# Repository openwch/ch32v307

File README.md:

# 32-bit Interconnected RISC-V MCU CH32V307/CH32V317
EN | [中文](README_zh.md)

### Overview
The CH32V305 and CH32V307/CH32V317 are interconnected microcontrollers, based on 32-bit RISC-V core, with hardware stack area and fast interrupt entry. Compared with standard RISC-V, the interrupt response speed is greatly improved. With single-precision float point instruction sets added and stack area extended, the CH32V305/7 has higher performance, the number of U(S)ART is extended to 8, and the number of motor timer is extended to 4. The CH32V305/7 provides USB2.0 high-speed interface (480Mbps) and has built-in PHY transceiver. CH32V307 Ethernet MAC is upgraded to GbE and integrates 10M PHY module.CH32V317 integrates 10M/100M PHY module

### System Block Diagram

### Features
- RISC-V4F processor, max 144MHz system clock frequency, RV32IMAFC instruction set;
- Single-cycle multiplication and hardware division, hardware float point unit (FPU) ;
- 64KB SRAM，256KB Flash;
- Supply voltage: 2.5V/3.3V, GPIO unit is supplied independently;
- Multiple low-power modes: sleep/stop/standby;
- Power-on/power-down reset (POR/PDR), programmable voltage detector (PVD);
- 2 general DMA controllers, 18 channels in total;
- 4 amplifiers;
- Single true random number generator (TRNG)
- 2 x 12-bit DAC;
- 2-unit 16-channel 12-bit ADC, 16-channel TouchKey;
- 10 timers;
- USB2.0 full-speed OTG interface;
- USB2.0 high-speed host/device interface (built-in 480Mbps PHY)
- 3 USARTs, 5 UARTs;
- 2 CAN interfaces (2.0B active);
- SDIO interface, FSMC interface, DVP;
- 2 x I2C, 3 x SPI, 2 x IIS;
- CH32V307 built-in Ethernet 10M PHY
- CH32V317 built-in Ethernet 10M/100M PHY
- CH32V307 80 I/O ports, can be mapped to 16 external interrupts;
- CH32V317 70 I/O ports, can be mapped to 16 external interrupts;
- CRC calculation unit, 96-bit unique chip ID;
- Serial 2-wire debug interface;
- Packages: LQFP64M, LQFP100,QFN68（CH32V317WCU6）.

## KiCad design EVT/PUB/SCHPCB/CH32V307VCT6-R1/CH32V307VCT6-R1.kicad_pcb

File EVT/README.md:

# EVT

### -- download URL
*  CH32V307EVT.ZIP-https://www.wch.cn/downloads/CH32V307EVT_ZIP.html

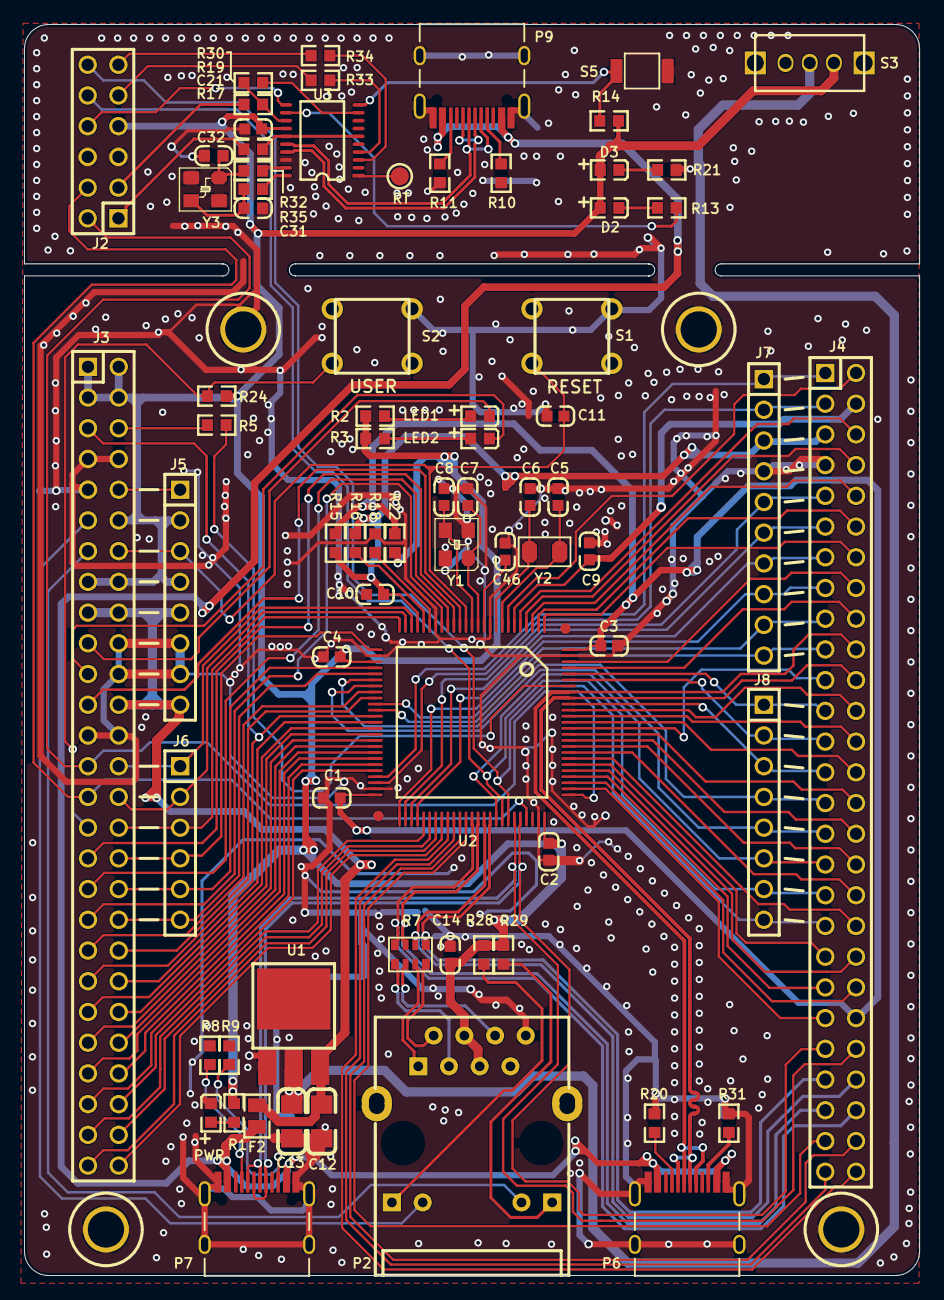
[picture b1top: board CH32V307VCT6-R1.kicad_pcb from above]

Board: 2 copper layers, 74.0 x 103.4 mm, 74 parts (0 on the bottom side), 137 nets.

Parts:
C1, C2, C3, C4, C9, C10, C11, C14, C21, C46: 0.1uF; 0603_C
C5, C6: 12pF; 0603_C
C7, C8: 22pF; 0603_C
C12, C13: 10uF; 3216_C
C31, C32: NC(22pF); 0603_C
D2: BLUE; 0603+
D3: RED; 0603+
F2: 500mA; 0805
J2: Header 6X2; IDC12-2.54mm
J3, J4: HEADER 27x2; IDC54-2.54MM
J5, J8: Header 8; SIP8-2.54mm
J6: Header 6; SIP6-2.54MM
J7: Header 10; SIP10-2.54mm
LED1: LED1 blue; 0603+
LED2: LED2 blue; 0603+
P2: HR911105A
P6: USBHS; TYPE-C-Receptacle-2.0
P7: USBFS; TYPE-C-Receptacle-2.0
P9: TYPE-C; TYPE-C-Receptacle-2.0
PWR: POWER red; 0603+
R1, R2, R3, R13, R21, R28, R29, R30: 1K; 0603
R5, R14, R24: 10K; 0603
R7: 0Ω; RCA-8P4R-0603
R8, R9, R10, R11, R20, R31: NC(5.1K); 0603
R15, R16, R18, R22: 0Ω; 0603
R17, R19: 100; 0603
R32, R35: NC(0R); 0603
R33, R34: 270; 0603
RT: Testpoint; TESTPOINT1
S1: RESET; KEYX
S2: USER; KEYX
S3: SW; SW1
S5: KEY; 贴片按键
U1: 1117-3.3V; SOT-223
U2: CH32V307V; LQFP100
U3: CH32V305F; TSSOP20
Y1: 8M; XT3225
Y2: 32.768k; FC-135
Y3: NC(12M); XT3225

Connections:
5V_in: F2.1, P6.A4, P6.B4, P7.A4, P7.B4, P9.A4, P9.B4
+5V: C12.1, F2.2, J3.17, J3.18, J3.24, J5.5, J5.8, U1.3
BOOT0: R5.2, U2.94
BOOT1: J3.5, J3.41, U2.37
CLK: J2.2, J3.27, U2.76
CLK0: J2.1, R17.1
DIO: J2.4, J3.29, U2.72
DIO0: J2.3, R19.1
D_SWCLK: R17.2, U3.6, U3.15
D_SWDIO: R19.2, R30.1, U3.13
ELED1: J3.11, P2.10
ELED2: J3.13, P2.11
ERXN: J4.49, R7.3, U2.64
ERXN1: P2.6, R7.6
ERXP: J4.50, R7.4, U2.63
ERXP1: P2.3, R7.5
ETXN: J4.47, R7.1, U2.66
ETXN1: P2.2, R7.8
ETXP: J4.48, R7.2, U2.65
ETXP1: P2.1, R7.7
GND: C1.1, C2.1, C3.2, C4.1, C5.2, C6.2, C7.1, C8.1, C9.1, C10.1, C11.1, C12.2, C13.2, C14.1, C21.2, C31.1, C32.1, C46.2, J2.5, J2.6, J3.7, J3.8, J3.9, J3.20, J3.22, J3.25, J3.26, J4.7, J5.6, J5.7, J7.4, P2.8, P6.0, P6.A1, P6.B1, P7.0, P7.A1, P7.B1, P9.0, P9.A1, P9.B1, PWR.2, R8.1, R9.1, R10.2, R11.2, R18.1, R20.1, R21.1, R31.1, S1.3, S2.3, S5.2, U1.1, U2.10, U2.19, U2.27, U2.49, U2.74, U2.99, U3.18, Y1.2, Y1.4, Y3.2, Y3.4
IAP: R14.1, S5.1, U3.10
KEY: J3.31, R24.1, S2.1
LED1: J3.19, LED1.2
LED2: J3.21, LED2.2
LED_CON: R13.1, U3.12
NRST: C11.2, J3.14, J5.3, S1.1, U2.14
NetC13_1: C13.1, S3.1, U1.2
NetD2_2: D2.2, R13.2
NetD3_2: D3.2, R21.2
NetJ3_6: J3.6, R5.1
NetJ3_10: J3.10, J5.1
NetLED1_1: LED1.1, R2.2
NetLED2_1: LED2.1, R3.2
NetP2_9: P2.9, R28.2
NetP2_12: P2.12, R29.2
NetP6_A5: P6.A5, R20.2
NetP6_B5: P6.B5, R31.2
NetP7_A5: P7.A5, R8.2
NetP7_B5: P7.B5, R9.2
NetP9_A5: P9.A5, R10.1
NetP9_B5: P9.B5, R11.1
NetPWR_1: PWR.1, R1.1
OSC_IN: C32.2, R32.2, Y3.1
OSC_OUT: C31.2, R35.2, Y3.3
PA0: J3.28, J6.1, U2.23
PA1: J3.30, J6.2, U2.24
PA2: J3.32, J6.3, U2.25
PA3: J3.34, J6.4, U2.26
PA4: J3.36, J6.5, U2.29
PA5: J3.38, J6.6, U2.30
PA6: J4.29, J8.4, U2.31
PA7: J4.31, J8.5, U2.32
PA8: J4.33, J8.6, U2.67
PA9: J2.10, J4.35, J8.7, U2.68
PA10: J2.12, J4.37, J8.8, U2.69
PA11: J4.46, P7.A7, P7.B7, U2.70
PA12: J4.45, P7.A6, P7.B6, U2.71
PA15: J4.43, U2.77
PB0: J4.17, J7.9, U2.35
PB1: J4.19, J7.10, U2.36
PB3: J4.26, U2.89
PB4: J4.24, U2.90
PB5: J4.27, J8.3, U2.91
PB6: J4.22, P6.A7, P6.B7, U2.92
PB7: J4.20, P6.A6, P6.B6, U2.93
PB8: J4.25, J8.2, U2.95
PB9: J4.23, J8.1, U2.96
PB10: J4.1, J7.1, U2.47
PB11: J4.3, J7.2, U2.48
PB12: J4.15, J7.8, U2.51
PB13: J4.9, J7.5, U2.52
PB14: J4.11, J7.6, U2.53
PB15: J4.13, J7.7, U2.54
PC0: J3.23, U2.15
PC1: J3.33, U2.16
PC2: J3.35, U2.17
PC3: J3.37, U2.18
PC4: J3.39, U2.33
PC5: J3.40, U2.34
PC6_305: R30.2, U3.9
PC10: J4.42, U2.78
PC11: J4.41, U2.79
PC12: J4.40, U2.80
PC13: J4.2, U2.7
PC14: C5.1, U2.8, Y2.1
PC15: C6.1, U2.9, Y2.2
PD0: J4.39, U2.81
PD0_305: R32.1, U3.19
PD1: J4.38, U2.82
PD1_305: R35.1, U3.20
PD2: J4.36, U2.83
PD3: J4.34, U2.84
PD4: J4.32, U2.85
PD5: J4.30, U2.86
PD6: J4.21, U2.87
PD7: J4.28, U2.88
PD8: J3.51, U2.55
PD9: J3.52, U2.56
PD10: J3.53, U2.57
PD11: J3.54, U2.58
PD12: J4.54, U2.59
PD13: J4.53, U2.60
PD14: J4.52, U2.61
PD15: J4.51, U2.62
PE0: J4.18, U2.97
PE1: J4.16, U2.98
PE2: J4.14, U2.1
PE3: J4.12, U2.2
PE4: J4.10, U2.3
PE5: J4.8, U2.4
PE6: J4.6, U2.5
PE7: J3.42, U2.38
PE8: J3.43, U2.39
PE9: J3.44, U2.40
PE10: J3.45, U2.41
PE11: J3.46, U2.42
PE12: J3.47, U2.43
PE13: J3.48, U2.44
PE14: J3.49, U2.45
PE15: J3.50, U2.46
RST0: J2.8, U3.11
RT: RT.1, U3.1
RX_OUT: J2.9, R33.1
TX_OUT: J2.11, R34.1
UART3_RX: R33.2, U3.4
UART3_TX: R34.2, U3.3
USB_N: P9.A7, P9.B7, U3.16
USB_P: P9.A6, P9.B6, U3.17
VBAT: C9.2, J4.4, U2.6
VCC: C2.2, C4.2, C14.2, C21.1, C46.1, D2.1, D3.1, J2.7, J3.1, J3.2, J3.3, J3.4, J3.12, J3.15, J3.16, J5.2, J5.4, P2.4, P2.5, R1.2, R2.1, R3.1, R14.2, R22.2, R24.2, R28.1, R29.1, S3.3, U2.11, U2.28, U2.75, U3.14
VDDA: C10.2, J4.5, J7.3, R15.2, R16.1, U2.22
VIO: C1.2, C3.1, J4.44, R15.1, R22.1, U2.50, U2.100
VREF+: R16.2, U2.21
VREF-: R18.2, U2.20
XI: C7.2, U2.12, Y1.1
XO: C8.2, U2.13, Y1.3

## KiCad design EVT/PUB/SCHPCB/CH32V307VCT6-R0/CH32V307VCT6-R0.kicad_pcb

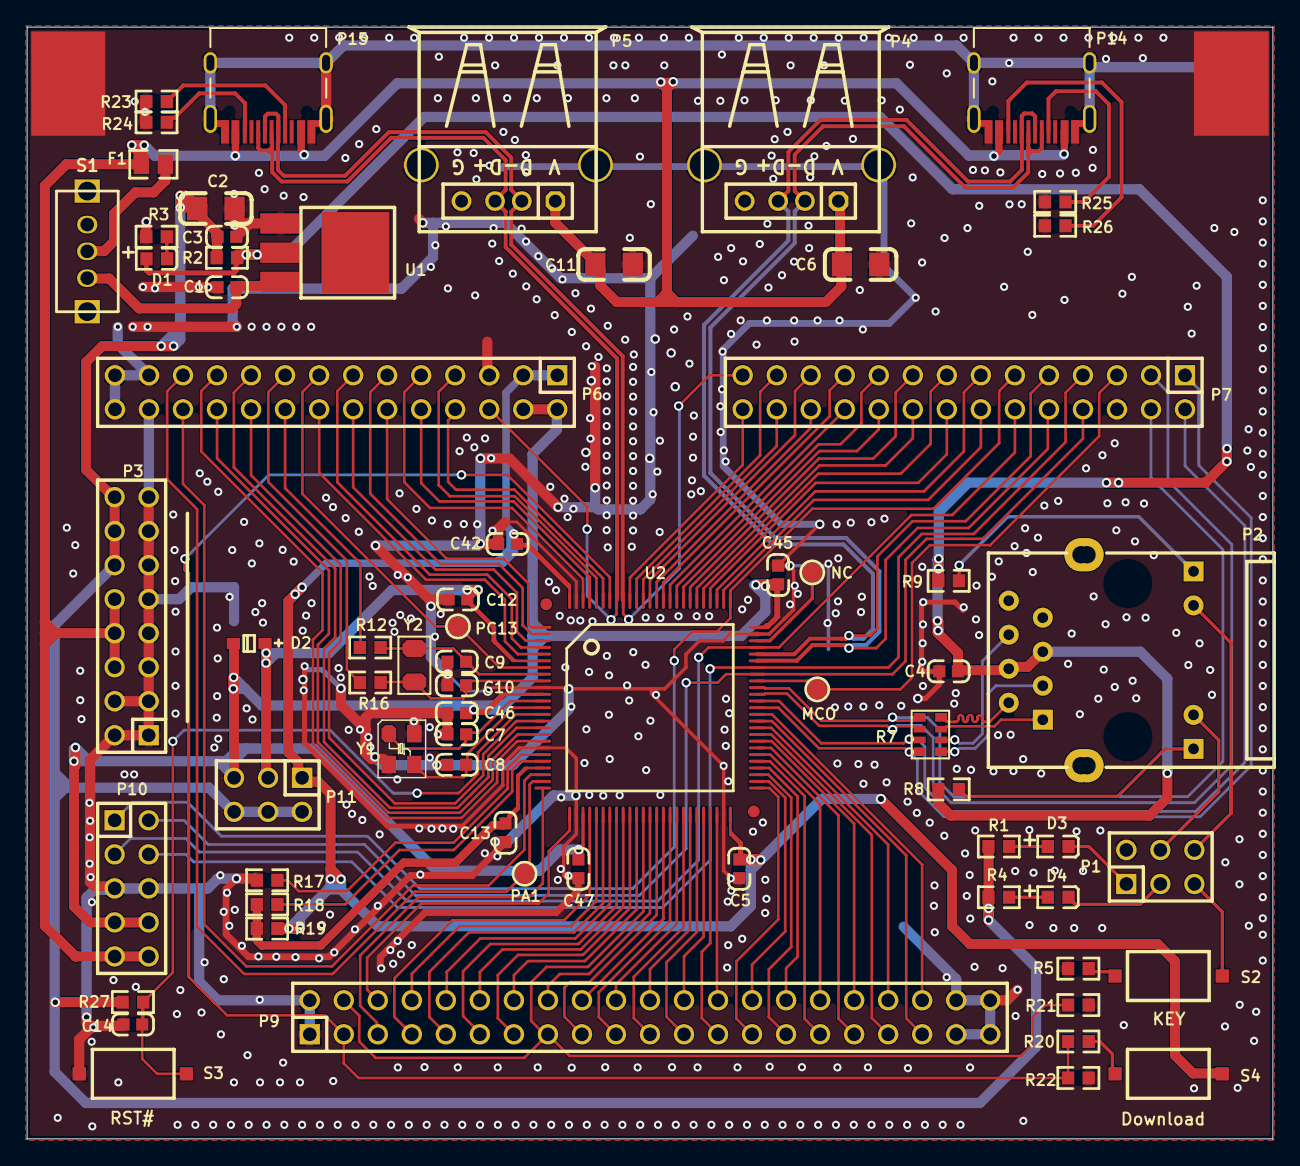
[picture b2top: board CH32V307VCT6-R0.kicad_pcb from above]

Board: 2 copper layers, 93.0 x 83.0 mm, 68 parts (0 on the bottom side), 119 nets.

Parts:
C1, C3, C4, C5, C12, C13, C14, C42, C45, C46, C47: 0.1uF; 0603_C
C2, C6, C11: 10uF; 3216_C
C7, C8: 22pF; 0603_C
C9, C10: 12pF; 0603_C
D1, D4: RED; 0603+
D2: B0520WS; SOD-323
D3: BLUE; 0603+
F1: 500mA; 0805
MCO: Testpoint; TESTPOINT1
NC: Testpoint; TESTPOINT1
P1: IO; IDC6-2.54mm
P2: HR911105A
P3: Ppin; IDC16-2.54mm
P4: USBFS; USBAF
P5: USBHS; USBAF
P6, P7: HEADER 14x2; IDC28-2.54MM
P9: HEADER 21x2; IDC42-2.54MM
P10: LINK; IDC10-2.54mm
P11: Psel; IDC6-2.54mm
P14: USBFS; TYPE-C-Receptacle-2.0
P15: USBHS; TYPE-C-Receptacle-2.0
PA1: Testpoint; TESTPOINT1
PC13: Testpoint; TESTPOINT1
R1, R3, R4, R8, R9, R20: 1K; 0603
R2, R17, R18, R19: 0R; 0603
R5, R21, R22, R27: 10K; 0603
R7: 0Ω; RCA-8P4R-0603
R12, R16: NC(0R); 0603
R23, R24, R25, R26: 5.1K; 0603
S1: SW SPDT; KEY2
S2: KEY; SMD_6.1x3.65x2.5mm-KEY
S3: RST#; SMD_6.1x3.65x2.5mm-KEY
S4: Download; SMD_6.1x3.65x2.5mm-KEY
U1: 1117-3.3V; SOT-223
U2: CH32V307V; LQFP100
Y1: 8MHz; XT3225
Y2: 32768Hz; FC-135

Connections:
3V3: C2.1, C3.1, P3.12, P3.14, P3.16, P11.2, P11.4, P11.6, R1.1, R2.1, R4.1, R27.2
3V3S: C4.2, D1.1, P2.4, P2.5, R2.2, R8.1, R9.1, U1.2
5V: C6.1, C11.1, F1.1, P3.6, P3.8, P3.10, P4.1, P5.1, P10.9, P10.10, P14.A4, P14.B4, P15.A4, P15.B4
BOOT0: P9.3, R20.1, R22.1, U2.94
BOOT1: P9.4, P9.15, R21.1, U2.37
ELED1: P1.4, P2.10
ELED2: P1.6, P2.11
ERXN: P7.2, R7.3, U2.64
ERXN1: P2.6, R7.6
ERXP: P7.1, R7.4, U2.63
ERXP1: P2.3, R7.5
ETXN: P7.4, R7.1, U2.66
ETXN1: P2.2, R7.8
ETXP: P7.3, R7.2, U2.65
ETXP1: P2.1, R7.7
GND: C1.2, C2.2, C3.2, C4.1, C5.2, C6.2, C7.1, C8.1, C9.1, C10.1, C11.2, C12.1, C13.2, C14.1, C42.1, C45.2, C46.2, C47.1, P1.2, P2.8, P3.1, P3.2, P3.3, P3.4, P3.5, P3.7, P3.9, P3.11, P3.13, P3.15, P4.0, P4.4, P5.0, P5.4, P6.5, P6.25, P6.26, P6.27, P6.28, P7.6, P9.1, P9.2, P9.39, P9.40, P9.41, P9.42, P10.5, P10.6, P14.0, P14.A1, P14.B1, P15.0, P15.A1, P15.B1, R3.2, R5.1, R17.1, R21.2, R22.2, R23.2, R24.2, R25.2, R26.2, S3.1, U1.1, U2.10, U2.19, U2.27, U2.49, U2.74, U2.99, Y1.2, Y1.4
KEY: P1.5, S2.1
LED1: D3.2, P1.1
LED2: D4.2, P1.3
MCO: MCO.1, P7.5, U2.67
NC: NC.1, U2.73
NRST: C14.2, R27.1, S3.2, U2.14
NetC1_1: C1.1, S1.2, U1.3
NetD1_2: D1.2, R3.1
NetD3_1: D3.1, R1.2
NetD4_1: D4.1, R4.2
NetF1_2: F1.2, S1.1
NetP2_9: P2.9, R8.2
NetP2_12: P2.12, R9.2
NetP14_A5: P14.A5, R25.1
NetP14_B5: P14.B5, R26.1
NetP15_A5: P15.A5, R23.1
NetP15_B5: P15.B5, R24.1
NetR5_2: R5.2, S2.2
NetR20_2: R20.2, S4.2
PA0: P6.24, U2.23
PA1: P6.23, PA1.1, U2.24
PA2: P9.5, U2.25
PA3: P9.6, U2.26
PA4: P9.7, U2.29
PA5: P9.8, U2.30
PA6: P9.9, U2.31
PA7: P9.10, U2.32
PA9: P7.8, P10.2, U2.68
PA10: P7.7, P10.4, U2.69
PA11: P4.2, P7.10, P14.A7, P14.B7, U2.70
PA12: P4.3, P7.9, P14.A6, P14.B6, U2.71
PA13: P7.12, P10.3, U2.72
PA14: P7.11, P10.1, U2.76
PA15: P7.14, U2.77
PB0: P9.13, U2.35
PB1: P9.14, U2.36
PB3: P7.26, U2.89
PB4: P7.25, U2.90
PB5: P7.28, U2.91
PB6: P5.2, P7.27, P15.A7, P15.B7, U2.92
PB7: P5.3, P6.6, P15.A6, P15.B6, U2.93
PB8: P6.8, U2.95
PB9: P6.7, U2.96
PB10: P9.25, U2.47
PB11: P9.26, U2.48
PB12: P9.27, U2.51
PB13: P9.28, U2.52
PB14: P9.29, U2.53
PB15: P9.30, U2.54
PC0: P6.20, U2.15
PC1: P6.19, U2.16
PC2: P6.22, U2.17
PC3: P6.21, U2.18
PC4: P9.11, U2.33
PC5: P9.12, U2.34
PC10: P7.13, U2.78
PC11: P7.16, U2.79
PC12: P7.15, U2.80
PC13: P6.15, PC13.1, U2.7
PC14: P6.18, R12.1
PC15: P6.17, R16.1
PD0: P7.18, U2.81
PD1: P7.17, U2.82
PD2: P7.20, U2.83
PD3: P7.19, U2.84
PD4: P7.22, U2.85
PD5: P7.21, U2.86
PD6: P7.24, U2.87
PD7: P7.23, U2.88
PD8: P9.31, U2.55
PD9: P9.32, U2.56
PD10: P9.33, U2.57
PD11: P9.34, U2.58
PD12: P9.35, U2.59
PD13: P9.36, U2.60
PD14: P9.37, U2.61
PD15: P9.38, U2.62
PE0: P6.10, U2.97
PE1: P6.9, U2.98
PE2: P6.12, U2.1
PE3: P6.11, U2.2
PE4: P6.14, U2.3
PE5: P6.13, U2.4
PE6: P6.16, U2.5
PE7: P9.16, U2.38
PE8: P9.17, U2.39
PE9: P9.18, U2.40
PE10: P9.19, U2.41
PE11: P9.20, U2.42
PE12: P9.21, U2.43
PE13: P9.22, U2.44
PE14: P9.23, U2.45
PE15: P9.24, U2.46
VBAT: C12.2, D2.1, P11.3, U2.6
VDD: C45.1, C46.1, C47.2, D2.2, P6.2, P6.4, P10.7, P10.8, P11.5, U2.11, U2.28, U2.75
VDDA: C13.1, R18.1, R19.2, U2.22
VIO: C5.1, C42.2, P6.1, P6.3, P11.1, R19.1, S4.1, U2.50, U2.100
VREF+: R18.2, U2.21
VREF-: R17.2, U2.20
X32KI: C9.2, R12.2, U2.8, Y2.1
X32KO: C10.2, R16.2, U2.9, Y2.2
XI: C7.2, U2.12, Y1.1
XO: C8.2, U2.13, Y1.3

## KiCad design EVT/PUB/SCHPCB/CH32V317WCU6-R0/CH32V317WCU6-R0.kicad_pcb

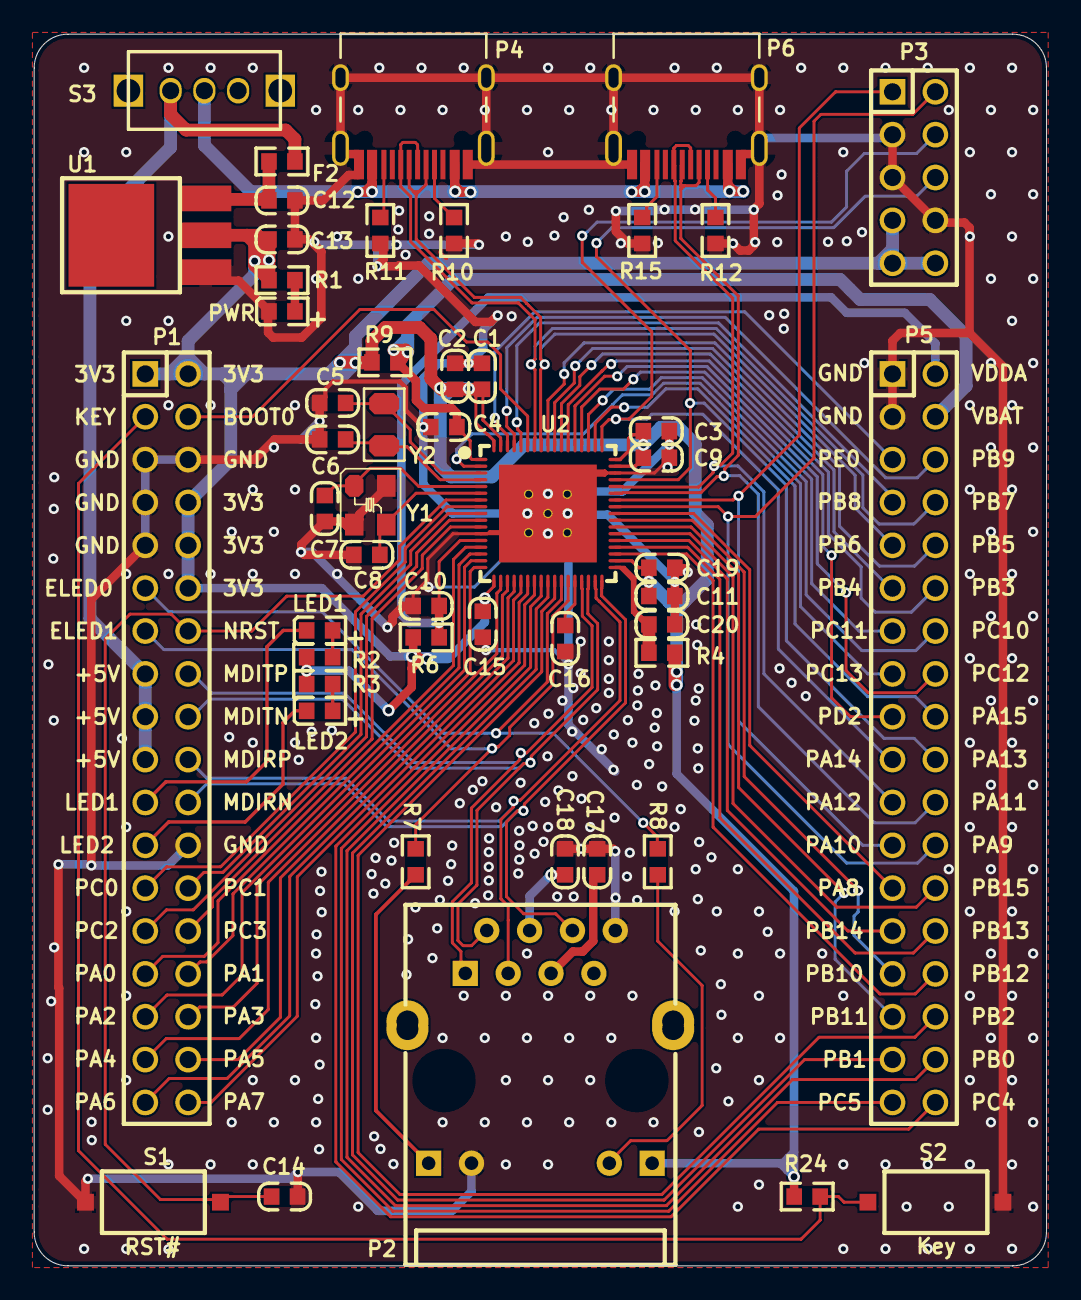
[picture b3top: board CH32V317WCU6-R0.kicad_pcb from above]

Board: 2 copper layers, 60.0 x 73.0 mm, 50 parts (0 on the bottom side), 79 nets.

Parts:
C1, C2, C3, C4, C9, C10, C11, C14, C15, C17, C18: 0.1uF; 0603_C
C5, C6: 12pF; 0603_C
C7, C8: 20pF; 0603_C
C12, C13, C19: 10uF; 0603_C
C16, C20: 1uF; 0603_C
F2: 500mA; 0603
LED1: LED1 blue; 0603+
LED2: LED2 blue; 0603+
P1, P5: Header 18X2; IDC36-2.54mm
P2: HR911105A
P3: Header 5X2; IDC10-2.54mm
P4: USBHS; TYPE-C-Receptacle-2.0
P6: USBFS; TYPE-C-Receptacle-2.0
PWR: POWER red; 0603+
R1, R2, R3: 1K; 0603
R4: 0Ω; 0603
R6, R9: 0R; 0603
R7, R8: 470Ω; 0603
R10, R11, R12, R15: NC(5.1K); 0603
R24: 10K; 0603
S1: RST#; SMD_6.1x3.65x2.5mm-KEY
S2: Key; SMD_6.1x3.65x2.5mm-KEY
S3: SW; SW1
U1: 1117-3.3V; SOT-223
U2: CH32V317W; QFN68_8X8
Y1: 8M; XT3225
Y2: 32.768k; FC-135

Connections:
3V3: C1.2, C2.2, C3.2, C9.2, C11.2, C13.1, C15.2, C19.2, P1.1, P1.2, P1.8, P1.10, P1.12, P2.12, P3.7, P3.9, P3.10, R1.2, R2.1, R3.1, R4.2, R6.1, R9.1, R24.2, U1.2, U2.18, U2.36, U2.50, U2.51, U2.67, U2.68
5V: P4.A4, P4.B4, P6.A4, P6.B4, S3.1
+5V: F2.1, P1.15, P1.17, P1.19, S3.3
BOOT0: P1.4, U2.63
ELED0: P1.11, R8.1, U2.28
ELED1: P1.13, R7.1, U2.29
GND: C1.1, C2.1, C3.1, C4.1, C5.2, C6.2, C7.1, C8.1, C9.1, C10.2, C11.1, C12.2, C13.2, C14.1, C15.1, C16.1, C17.1, C18.1, C19.1, C20.1, P1.5, P1.6, P1.7, P1.9, P1.24, P2.8, P2.10, P3.3, P3.5, P3.8, P4.0, P4.A1, P4.B1, P5.1, P5.3, P6.0, P6.A1, P6.B1, PWR.2, R10.1, R11.1, R12.1, R15.1, S1.1, S2.2, U1.1, U2.0, U2.12, U2.49, Y1.2, Y1.4
KEY: P1.3, R24.1, S2.1
LED1: LED1.2, P1.21
LED2: LED2.2, P1.23
MDIRN: P1.22, P2.6, U2.34
MDIRP: P1.20, P2.3, U2.33
MDITN: P1.18, P2.2, U2.32
MDITP: P1.16, P2.1, U2.31
NRST: C14.2, P1.14, S1.2, U2.7
NetC12_1: C12.1, F2.2, U1.3
NetC17_2: C17.2, P2.5
NetC18_2: C18.2, P2.4
NetLED1_1: LED1.1, R2.2
NetLED2_1: LED2.1, R3.2
NetP2_9: P2.9, R7.2
NetP2_11: P2.11, R8.2
NetP4_A5: P4.A5, R10.2
NetP4_B5: P4.B5, R11.2
NetP6_A5: P6.A5, R12.2
NetP6_B5: P6.B5, R15.2
NetPWR_1: PWR.1, R1.1
PA0: P1.29, U2.14
PA1: P1.30, U2.15
PA2: P1.31, U2.16
PA3: P1.32, U2.17
PA4: P1.33, U2.19
PA5: P1.34, U2.20
PA6: P1.35, U2.21
PA7: P1.36, U2.22
PA8: P5.25, U2.43
PA9: P3.2, P5.24, U2.44
PA10: P3.1, P5.23, U2.45
PA11: P5.22, P6.A7, P6.B7, U2.46
PA12: P5.21, P6.A6, P6.B6, U2.47
PA13: P3.6, P5.20, U2.48
PA14: P3.4, P5.19, U2.52
PA15: P5.18, U2.53
PB0: P5.34, U2.25
PB1: P5.33, U2.26
PB2: P5.32, U2.27
PB3: P5.12, U2.58
PB4: P5.11, U2.59
PB5: P5.10, U2.60
PB6: P4.A7, P4.B7, P5.9, U2.61
PB7: P4.A6, P4.B6, P5.8, U2.62
PB8: P5.7, U2.64
PB9: P5.6, U2.65
PB10: P5.29, U2.42
PB11: P5.31, U2.41
PB12: P5.30, U2.37
PB13: P5.28, U2.38
PB14: P5.27, U2.39
PB15: P5.26, U2.40
PC0: P1.25, U2.8
PC1: P1.26, U2.9
PC2: P1.27, U2.10
PC3: P1.28, U2.11
PC4: P5.36, U2.23
PC5: P5.35, U2.24
PC10: P5.14, U2.54
PC11: P5.13, U2.55
PC12: P5.16, U2.56
PC13: P5.15, U2.2
PD2: P5.17, U2.57
PE0: P5.5, U2.66
VBAT: C4.2, P5.4, R9.2, U2.1
VDDA: C10.1, P5.2, R6.2, U2.13
VDDK: C16.2, U2.30
VDD_ETH: C20.2, R4.1, U2.35
X32KI: C5.1, U2.3, Y2.1
X32KO: C6.1, U2.4, Y2.2
XI: C7.2, U2.5, Y1.1
XO: C8.2, U2.6, Y1.3

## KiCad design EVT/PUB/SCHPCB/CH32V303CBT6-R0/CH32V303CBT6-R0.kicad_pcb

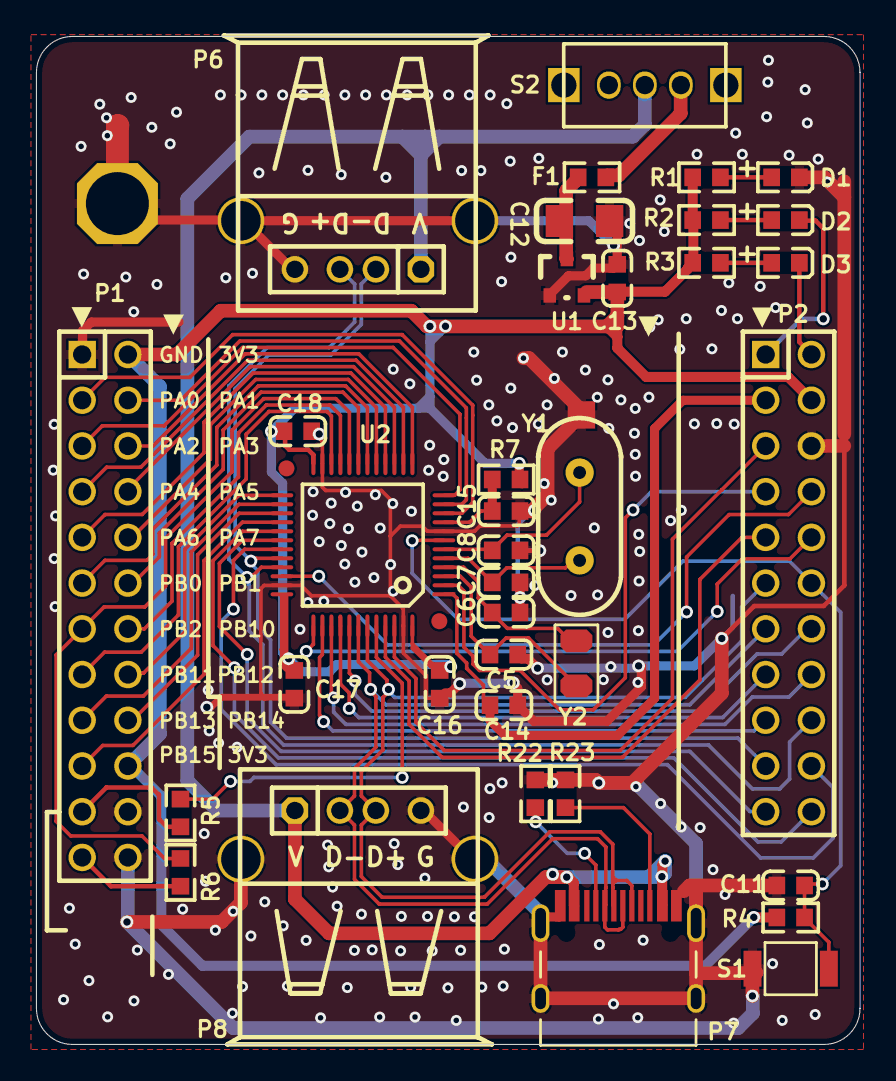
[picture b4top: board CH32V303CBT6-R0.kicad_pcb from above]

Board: 2 copper layers, 45.8 x 56.0 mm, 36 parts (0 on the bottom side), 55 nets.

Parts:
C5, C6: 12pF; 0603_C
C7, C8: 22pF; 0603_C
C11, C14, C15, C16, C17, C18: 0.1uF; 0603_C
C12: 10uF; 3216_C
C13: 2.2uF; 0603_C
D1: POWER red; 0603+
D2: LED1; 0603+
D3: LED2; 0603+
F1: 500mA; 0603
P1: HEADER 12x2; IDC24-2.54MM
P2: HEADER 11x2; IDC22-2.54MM
P6, P8: USB_A; USBAF
P7: TYPE-C; TYPE-C-Receptacle-2.0
R1, R2, R3: 1K; 0603
R4, R5, R6: 10K; 0603
R7: 0Ω; 0603
R22, R23: NC(5.1K); 0603
S1: KEY; 贴片按键
S2: SW; KEY2
U1: 6219P33M; SOT-23
U2: CH32V203CxT; LQFP48
Y1: 8M; XT_AT49
Y2: 32.768k; FC-135

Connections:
+5V: P6.1, P7.A4, P7.B4, P8.1, S2.1
BOOT0: R5.1, U2.44
BOOT1: P1.13, R6.1, U2.20
GND: C5.2, C6.2, C7.1, C8.1, C11.1, C12.2, C13.2, C14.2, C15.2, C16.1, C17.1, C18.1, D1.2, P1.1, P1.22, P1.24, P2.6, P6.0, P6.4, P7.0, P7.A1, P7.B1, P8.0, P8.4, R22.2, R23.2, S1.2, U1.1, U2.8, U2.23, U2.35, U2.47, Y1.0
LED1: D2.2, P2.1
LED2: D3.2, P2.2
NRST: C11.2, P2.12, R4.1, S1.1, U2.7
NetD1_1: D1.1, R1.1
NetD2_1: D2.1, R2.2
NetD3_1: D3.1, R3.2
NetF1_1: F1.1, S2.3
NetP1_21: P1.21, R5.2
NetP1_23: P1.23, R6.2
NetP7_A5: P7.A5, R22.1
NetP7_B5: P7.B5, R23.1
PA0: P1.3, U2.10
PA1: P1.4, U2.11
PA2: P1.5, U2.12
PA3: P1.6, U2.13
PA4: P1.7, U2.14
PA5: P1.8, U2.15
PA6: P1.9, U2.16
PA7: P1.10, U2.17
PA8: P2.22, U2.29
PA9: P2.21, U2.30
PA10: P2.20, U2.31
PA11: P2.19, P6.2, U2.32
PA12: P2.18, P6.3, U2.33
PA13: P2.8, U2.34
PA14: P2.10, U2.37
PA15: P2.17, U2.38
PB0: P1.11, U2.18
PB1: P1.12, U2.19
PB3: P2.16, U2.39
PB4: P2.15, U2.40
PB5: P2.14, U2.41
PB6: P2.13, P7.A7, P7.B7, P8.2, U2.42
PB7: P2.11, P7.A6, P7.B6, P8.3, U2.43
PB8: P2.9, U2.45
PB9: P2.5, U2.46
PB10: P1.14, U2.21
PB11: P1.15, U2.22
PB12: P1.16, U2.25
PB13: P1.17, U2.26
PB14: P1.18, U2.27
PB15: P1.19, U2.28
PC13: P2.7, U2.2
PC14: C5.1, U2.3, Y2.1
PC15: C6.1, U2.4, Y2.2
PD0: C7.2, U2.5, Y1.2
PD1: C8.2, U2.6, Y1.1
V5V: C12.1, F1.2, U1.3
VBAT: C14.1, P2.3, U2.1
VCC: C13.1, C16.2, C17.2, C18.2, P1.2, P1.20, P2.4, R1.2, R2.1, R3.1, R4.2, R7.1, U1.2, U2.24, U2.36, U2.48
VDDA: C15.1, R7.2, U2.9

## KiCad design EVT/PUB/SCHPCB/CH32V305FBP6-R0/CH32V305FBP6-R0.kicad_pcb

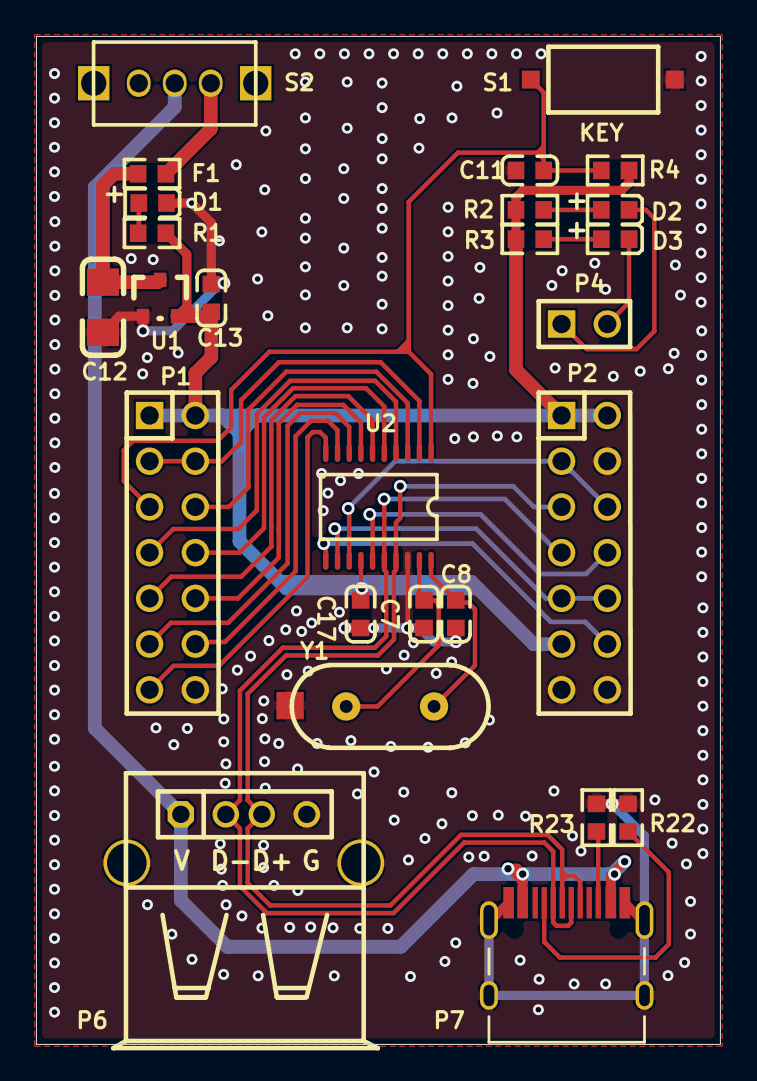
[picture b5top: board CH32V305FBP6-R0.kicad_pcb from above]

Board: 2 copper layers, 38.0 x 56.0 mm, 26 parts (0 on the bottom side), 30 nets.

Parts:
C7, C8: 22pF; 0603_C
C11, C17: 0.1uF; 0603_C
C12: 10uF; 3216_C
C13: 2.2uF; 0603_C
D1: POWER red; 0603+
D2: LED1; 0603+
D3: LED2; 0603+
F1: 500mA; 0603
P1, P2: HEADER 7x2; IDC14-2.54mm
P4: 2HEAD; SIP2-2.54mm
P6: USB_A; USBAF
P7: TYPE-C; TYPE-C-Receptacle-2.0
R1, R2, R3: 1K; 0603
R4: 10K; 0603
R22, R23: NC(5.1K); 0603
S1: KEY; SMD_6.1x3.65x2.5mm-KEY
S2: SW; KEY2
U1: 6219; SOT-23
U2: CH32V305F; TSSOP20
Y1: 8M; XT_AT49

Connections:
+5V: P6.1, P7.A4, P7.B4, S2.1
GND: C7.1, C8.1, C11.1, C12.2, C13.1, C17.1, D1.2, P1.14, P2.4, P2.13, P2.14, P6.0, P6.4, P7.0, P7.A1, P7.B1, R22.2, R23.2, S1.2, U1.1, U2.18, Y1.0
LED1: D2.2, P4.1
LED2: D3.2, P4.2
NRST: C11.2, P1.5, R4.1, S1.1, U2.1
NetD1_1: D1.1, R1.1
NetD2_1: D2.1, R2.2
NetD3_1: D3.1, R3.2
NetF1_1: F1.1, S2.3
NetP7_A5: P7.A5, R22.1
NetP7_B5: P7.B5, R23.1
PA1: P1.3, P1.4, U2.2
PA8: P2.9, P2.10, U2.12
PA9: P2.3, P2.6, U2.13
PA14: P2.8, U2.15
PB6: P2.7, P6.2, P7.A7, P7.B7, U2.16
PB7: P2.5, P6.3, P7.A6, P7.B6, U2.17
PB10: P1.6, U2.3
PB11: P1.7, U2.4
PB12: P1.8, U2.5
PB13: P1.9, U2.6
PB14: P1.10, U2.7
PB15: P1.11, U2.8
PC6: P1.12, U2.9
PC7: P1.13, U2.10
PC8: P2.12, U2.11
PD0: C7.2, U2.19, Y1.2
PD1: C8.2, U2.20, Y1.1
V5V: C12.1, F1.2, U1.3
VCC: C13.2, C17.2, P1.1, P1.2, P2.1, P2.2, P2.11, R1.2, R2.1, R3.1, R4.2, U1.2, U2.14

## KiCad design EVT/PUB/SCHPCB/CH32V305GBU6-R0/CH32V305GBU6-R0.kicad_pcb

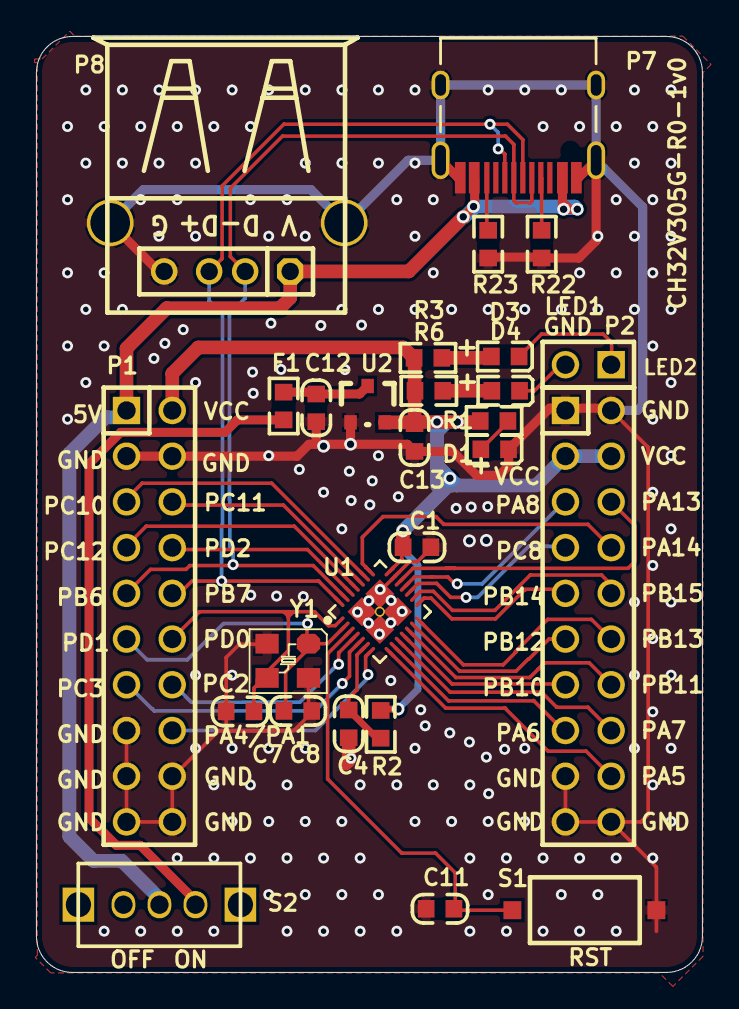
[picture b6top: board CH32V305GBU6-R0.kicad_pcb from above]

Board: 2 copper layers, 37.0 x 52.0 mm, 27 parts (0 on the bottom side), 38 nets.

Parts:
C1, C4, C11: 0.1uF; 0603_C
C7, C8: 22pF; 0603_C
C12: 10uF; 0603_C
C13: 2.2uF; 0603_C
D1: POWER red; 0603+
D3: LED2; 0603+
D4: LED1; 0603+
F1: 500mA; 0603
P1, P2: Header 10X2; IDC20-2.54mm
P4: HEADER 2; SIP2-2.54mm
P7: TYPE-C; TYPE-C-Receptacle-2.0
P8: USB_A; USBAF
R1, R2, R3, R6: 1K; 0603
R22, R23: 5.1K; 0603
S1: RST; SMD_6.1x3.65x2.5mm-KEY
S2: SW; SW1
U1: CH32V305GBU6; QFN28_4X4
U2: 6219P33M; SOT-23
Y1: 8M; XT3225

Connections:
GND: C1.2, C4.2, C7.1, C8.1, C11.1, C12.2, C13.2, D1.2, P1.3, P1.4, P1.15, P1.17, P1.18, P1.19, P1.20, P2.1, P2.2, P2.17, P2.19, P2.20, P7.0, P7.A1, P7.B1, P8.0, P8.4, R22.2, R23.2, S1.2, U1.0, U1.20, U2.1, Y1.2, Y1.4
LED1: D4.2, P4.2
LED2: D3.2, P4.1
NetD1_1: D1.1, R1.1
NetD3_1: D3.1, R3.2
NetD4_1: D4.1, R6.2
NetF1_1: F1.1, S2.3
NetP7_A5: P7.A5, R22.1
NetP7_B5: P7.B5, R23.1
PA4/PA1: P1.16, U1.7
PA5: P2.18, U1.8
PA6: P2.15, U1.9
PA7: P2.16, U1.10
PA8: P2.5, U1.18
PA13: P2.6, U1.19
PA14: P2.8, U1.22
PB6: P1.9, P7.A7, P7.B7, P8.2, U1.27
PB7: P1.10, P7.A6, P7.B6, P8.3, U1.28
PB10: P2.13, U1.11
PB11: P2.14, U1.12
PB12: P2.11, U1.13
PB13: P2.12, U1.14
PB14: P2.9, U1.15
PB15: P2.10, U1.16
PC2: P1.14, U1.4
PC3: P1.13, U1.5
PC8: P2.7, U1.17
PC10: P1.5, U1.23
PC11: P1.6, U1.24
PC12: P1.7, U1.25
PD0: C7.2, P1.12, U1.1, Y1.3
PD1: C8.2, P1.11, U1.2, Y1.1
PD2: P1.8, U1.26
RST: C11.2, S1.1, U1.3
V5V: C12.1, F1.2, U2.3
VBUS: P1.1, P7.A4, P7.B4, P8.1, S2.1
VCC: C1.1, C13.1, P1.2, P2.3, P2.4, R1.2, R2.1, R3.1, R6.1, U1.21, U2.2
VIO: C4.1, R2.2, U1.6

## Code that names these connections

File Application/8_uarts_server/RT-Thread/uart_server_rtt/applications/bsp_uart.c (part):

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 *
 *  @brief   initialize uart1~uart8 io
 *
 *           UART1  TX-->PA9   RX-->PA10
 *           UART2  TX-->PA2   RX-->PA3
 *           UART3  TX-->PB10  RX-->PB11
 *           UART4  TX-->PC10  RX-->PC11
 *           UART5  TX-->PC12  RX-->PD2
 *           UART6  TX-->PC0   RX-->PC1
 *           UART7  TX-->PC2   RX-->PC3
 *           UART8  TX-->PC4   RX-->PC5
 *
 *  @param   none
 *
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    		               RCC_APB2Periph_GPIOC|RCC_APB2Periph_GPIOD, ENABLE);


    /* UART1 TX-->PA9   RX-->PA10 */
//	GPIO_InitStructure.GPIO_Pin = GPIO_Pin_9;
//	GPIO_InitStructure.GPIO_Speed = GPIO_Speed_50MHz;
//	GPIO_InitStructure.GPIO_Mode = GPIO_Mode_AF_PP;
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//	GPIO_Init(GPIOA, &GPIO_InitStructure);


    /* USART2 TX-->PA2   RX-->PA3 */
    GPIO_InitStructure.GPIO_Pin = GPIO_Pin_2;
    GPIO_InitStructure.GPIO_Speed = GPIO_Speed_50MHz;
    GPIO_InitStructure.GPIO_Mode = GPIO_Mode_AF_PP;
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    GPIO_Init(GPIOA, &GPIO_InitStructure);


    /* USART3 TX-->PB10  RX-->PB11 */
	GPIO_InitStructure.GPIO_Pin = GPIO_Pin_10;
	GPIO_InitStructure.GPIO_Speed = GPIO_Speed_50MHz;
	GPIO_InitStructure.GPIO_Mode = GPIO_Mode_AF_PP;
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	GPIO_InitStructure.GPIO_Mode = GPIO_Mode_IN_FLOATING;
	GPIO_Init(GPIOB, &GPIO_InitStructure);

	/* USART4 TX-->PC10  RX-->PC11 */
	GPIO_InitStructure.GPIO_Pin = GPIO_Pin_10;
	GPIO_InitStructure.GPIO_Speed = GPIO_Speed_50MHz;
	GPIO_InitStructure.GPIO_Mode = GPIO_Mode_AF_PP;
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	GPIO_InitStructure.GPIO_Mode = GPIO_Mode_IN_FLOATING;
	GPIO_Init(GPIOC, &GPIO_InitStructure);

	/* USART5 TX-->PC12  RX-->PD2 */
	GPIO_InitStructure.GPIO_Pin = GPIO_Pin_12;
	GPIO_InitStructure.GPIO_Speed = GPIO_Speed_50MHz;
	GPIO_InitStructure.GPIO_Mode = GPIO_Mode_AF_PP;
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	GPIO_InitStructure.GPIO_Mode = GPIO_Mode_IN_FLOATING;
	GPIO_Init(GPIOD, &GPIO_InitStructure);

	/* USART6 TX-->PC0  RX-->PC1 */
	GPIO_InitStructure.GPIO_Pin = GPIO_Pin_0;
	GPIO_InitStructure.GPIO_Speed = GPIO_Speed_50MHz;
	GPIO_InitStructure.GPIO_Mode = GPIO_Mode_AF_PP;
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	GPIO_InitStructure.GPIO_Mode = GPIO_Mode_IN_FLOATING;
	GPIO_Init(GPIOC, &GPIO_InitStructure);

	/* USART7 TX-->PC2  RX-->PC3 */
	GPIO_InitStructure.GPIO_Pin = GPIO_Pin_2;
	GPIO_InitStructure.GPIO_Speed = GPIO_Speed_50MHz;
	GPIO_InitStructure.GPIO_Mode = GPIO_Mode_AF_PP;
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	GPIO_InitStructure.GPIO_Mode = GPIO_Mode_IN_FLOATING;
	GPIO_Init(GPIOC, &GPIO_InitStructure);

	/* USART8 TX-->PC4  RX-->PC5 */
	GPIO_InitStructure.GPIO_Pin = GPIO_Pin_4;
	GPIO_InitStructure.GPIO_Speed = GPIO_Speed_50MHz;
	GPIO_InitStructure.GPIO_Mode = GPIO_Mode_AF_PP;
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	UART_GPIO_Init();
	USART_InitTypeDef USART_InitStructure={0};

	/* USART1 TX-->PA9   RX-->PA10 */
//	uart_data_t[0].RX_buffer = &UART1_RX_DMA_DataBuf[0];
//	uart_data_t[0].TX_buffer = &UART1_TX_DMA_DataBuf[0];
//	uart_data_t[0].TX_data_length = &UART1_TX_Buf_Length[0];
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//	USART_Init(USART1, &USART_InitStructure);
//	USART_Cmd(USART1, ENABLE);

	/* USART2 TX-->PA2   RX-->PA3 */
	uart_data_t[1].RX_buffer = &UART2_RX_DMA_DataBuf[0];
	uart_data_t[1].TX_buffer = &UART2_TX_DMA_DataBuf[0];
	uart_data_t[1].TX_data_length = &UART2_TX_Buf_Length[0];
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	USART_Init(USART2, &USART_InitStructure);
	USART_Cmd(USART2, ENABLE);

	/* USART3 TX-->PB10  RX-->PB11 */
	uart_data_t[2].RX_buffer = &UART3_RX_DMA_DataBuf[0];
	uart_data_t[2].TX_buffer = &UART3_TX_DMA_DataBuf[0];
	uart_data_t[2].TX_data_length = &UART3_TX_Buf_Length[0];
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	USART_Cmd(USART3, ENABLE);


	/* USART4 TX-->PC10  RX-->PC11 */
	uart_data_t[3].RX_buffer = &UART4_RX_DMA_DataBuf[0];
	uart_data_t[3].TX_buffer = &UART4_TX_DMA_DataBuf[0];
	uart_data_t[3].TX_data_length = &UART4_TX_Buf_Length[0];
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    USART_Init(UART4, &USART_InitStructure);
    USART_Cmd(UART4, ENABLE);

	/* USART5 TX-->PC12  RX-->PD2 */
	uart_data_t[4].RX_buffer = &UART5_RX_DMA_DataBuf[0];
	uart_data_t[4].TX_buffer = &UART5_TX_DMA_DataBuf[0];
	uart_data_t[4].TX_data_length = &UART5_TX_Buf_Length[0];
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    USART_Init(UART5, &USART_InitStructure);
    USART_Cmd(UART5, ENABLE);

	/* USART6 TX-->PC0  RX-->PC1 */
	uart_data_t[5].RX_buffer = &UART6_RX_DMA_DataBuf[0];
	uart_data_t[5].TX_buffer = &UART6_TX_DMA_DataBuf[0];
	uart_data_t[5].TX_data_length = &UART6_TX_Buf_Length[0];
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    USART_Init(UART6, &USART_InitStructure);
    USART_Cmd(UART6, ENABLE);

	/* UART7  TX-->PC2   RX-->PC3 */
	uart_data_t[6].RX_buffer = &UART7_RX_DMA_DataBuf[0];
	uart_data_t[6].TX_buffer = &UART7_TX_DMA_DataBuf[0];
	uart_data_t[6].TX_data_length = &UART7_TX_Buf_Length[0];
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    USART_Cmd(UART7, ENABLE);


	/* UART8  TX-->PC4   RX-->PC5 */
	uart_data_t[7].RX_buffer = &UART8_RX_DMA_DataBuf[0];
	uart_data_t[7].TX_buffer = &UART8_TX_DMA_DataBuf[0];
	uart_data_t[7].TX_data_length = &UART8_TX_Buf_Length[0];
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
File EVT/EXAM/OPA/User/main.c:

/********************************** (C) COPYRIGHT *******************************
* File Name          : main.c
* Author             : WCH
* Version            : V1.0.0
* Date               : 2021/06/06
* Description        : Main program body.
*********************************************************************************
* Copyright (c) 2021 Nanjing Qinheng Microelectronics Co., Ltd.
* Attention: This software (modified or not) and binary are used for 
* microcontroller manufactured by Nanjing Qinheng Microelectronics.
*******************************************************************************/

/*
 *@Note
 OPA4 is used as voltage follower output, DAC outputs to OPA4, ADC samples OPA4
 DAC_CH1--PA4
 OPA4_CHP1--PC4
 OPA4_CHN1--PC3
 OPA4_OUT_IO_OUT0--PA0

  In this example, PA0 and PC3 are short-circuited, and PA4 is connected to PC4.
  If the negative feedback is connected to a resistor, it can also form an
  operational amplifier.
*/

#include "debug.h"

/* Global define */


/* Global Variable */ 
s16 Calibrattion_Val = 0;


/*********************************************************************
 * @fn      OPA4_Init
 *
 * @brief   Initializes OPA4 collection.
 *
 * @return  none
 */
void OPA4_Init(void)
{
    GPIO_InitTypeDef GPIO_InitStructure={0};
    OPA_InitTypeDef  OPA_InitStructure={0};

    RCC_APB2PeriphClockCmd(RCC_APB2Periph_GPIOC, ENABLE );
    GPIO_InitStructure.GPIO_Pin = GPIO_Pin_4|GPIO_Pin_3;
    GPIO_InitStructure.GPIO_Mode = GPIO_Mode_IN_FLOATING;
    GPIO_InitStructure.GPIO_Speed = GPIO_Speed_50MHz;
    GPIO_Init(GPIOC, &GPIO_InitStructure);

    OPA_InitStructure.OPA_NUM=OPA4;
    OPA_InitStructure.PSEL=CHP1;
    OPA_InitStructure.NSEL=CHN1;
    OPA_InitStructure.Mode=OUT_IO_OUT0;
    OPA_Init(&OPA_InitStructure);
    OPA_Cmd(OPA4,ENABLE);

}

/*********************************************************************
 * @fn      Dac_Channel1_Init
 *
 * @brief   Initializes DAC Channel1 collection.
 *
 * @return  none
 */
void Dac_Channel1_Init(void)
{
	GPIO_InitTypeDef GPIO_InitStructure={0};
	DAC_InitTypeDef DAC_InitType={0};
	
	RCC_APB2PeriphClockCmd(RCC_APB2Periph_GPIOA, ENABLE );
	RCC_APB1PeriphClockCmd(RCC_APB1Periph_DAC, ENABLE );
	
	GPIO_InitStructure.GPIO_Pin = GPIO_Pin_4;
 	GPIO_InitStructure.GPIO_Mode = GPIO_Mode_AIN; 		     
 	GPIO_InitStructure.GPIO_Speed = GPIO_Speed_50MHz;
 	GPIO_Init(GPIOA, &GPIO_InitStructure);
	GPIO_SetBits(GPIOA,GPIO_Pin_4);
	
	DAC_InitType.DAC_Trigger=DAC_Trigger_None;
	DAC_InitType.DAC_WaveGeneration=DAC_WaveGeneration_None;
	DAC_InitType.DAC_LFSRUnmask_TriangleAmplitude=DAC_TriangleAmplitude_4095;
	DAC_InitType.DAC_OutputBuffer=DAC_OutputBuffer_Enable ;
    DAC_Init(DAC_Channel_1,&DAC_InitType);
    DAC_Cmd(DAC_Channel_1, ENABLE);


    DAC_SetChannel1Data(DAC_Align_12b_R, 0);
}

/*********************************************************************
 * @fn      main
 *
 * @brief   ADC_Channel0_Init
 *
 * @return  none
 */
void ADC_Channel0_Init(void)
{
    GPIO_InitTypeDef GPIO_InitStructure={0};
    ADC_InitTypeDef ADC_InitStructure={0};

    RCC_APB2PeriphClockCmd(RCC_APB2Periph_GPIOA, ENABLE );
    RCC_APB2PeriphClockCmd(RCC_APB2Periph_ADC1, ENABLE );
    RCC_ADCCLKConfig(RCC_PCLK2_Div8);

    GPIO_InitStructure.GPIO_Pin = GPIO_Pin_0;
    GPIO_InitStructure.GPIO_Mode = GPIO_Mode_AIN;
    GPIO_InitStructure.GPIO_Speed = GPIO_Speed_50MHz;
    GPIO_Init(GPIOA, &GPIO_InitStructure);

    ADC_InitStructure.ADC_Mode = ADC_Mode_Independent;
    ADC_InitStructure.ADC_ScanConvMode = DISABLE;
    ADC_InitStructure.ADC_ContinuousConvMode = DISABLE;
    ADC_InitStructure.ADC_ExternalTrigConv = ADC_ExternalTrigConv_None;
    ADC_InitStructure.ADC_DataAlign = ADC_DataAlign_Right;
    ADC_InitStructure.ADC_NbrOfChannel = 1;
    ADC_Init(ADC1, &ADC_InitStructure);

    ADC_Cmd(ADC1, ENABLE);

    ADC_BufferCmd(ADC1, DISABLE);   //disable buffer
    ADC_ResetCalibration(ADC1);
    while(ADC_GetResetCalibrationStatus(ADC1));
    ADC_StartCalibration(ADC1);
    while(ADC_GetCalibrationStatus(ADC1));
    Calibrattion_Val = Get_CalibrationValue(ADC1);

    ADC_BufferCmd(ADC1, ENABLE);   //enable buffer
}

/*********************************************************************
 * @fn      Get_ADC_Val
 *
 * @brief   Returns ADCx conversion result data.
 *
 * @param   ch - ADC channel.
 *            ADC_Channel_0 - ADC Channel0 selected.
 *            ADC_Channel_1 - ADC Channel1 selected.
 *            ADC_Channel_2 - ADC Channel2 selected.
 *            ADC_Channel_3 - ADC Channel3 selected.
 *            ADC_Channel_4 - ADC Channel4 selected.
 *            ADC_Channel_5 - ADC Channel5 selected.
 *            ADC_Channel_6 - ADC Channel6 selected.
 *            ADC_Channel_7 - ADC Channel7 selected.
 *            ADC_Channel_8 - ADC Channel8 selected.
 *            ADC_Channel_9 - ADC Channel9 selected.
 *            ADC_Channel_10 - ADC Channel10 selected.
 *            ADC_Channel_11 - ADC Channel11 selected.
 *            ADC_Channel_12 - ADC Channel12 selected.
 *            ADC_Channel_13 - ADC Channel13 selected.
 *            ADC_Channel_14 - ADC Channel14 selected.
 *            ADC_Channel_15 - ADC Channel15 selected.
 *            ADC_Channel_16 - ADC Channel16 selected.
 *            ADC_Channel_17 - ADC Channel17 selected.
 *
 * @return  none
 */
u16 Get_ADC_Val(u8 ch)
{
  u16 val;

    ADC_RegularChannelConfig(ADC1, ch, 1, ADC_SampleTime_239Cycles5 );
    ADC_SoftwareStartConvCmd(ADC1, ENABLE);

    while(!ADC_GetFlagStatus(ADC1, ADC_FLAG_EOC ));

    val = ADC_GetConversionValue(ADC1);

    return val;
}

/*********************************************************************
 * @fn      Get_ADC_Average
 *
 * @brief   Returns ADCx conversion result average data.
 *
 * @param   ch - ADC channel.
 *            ADC_Channel_0 - ADC Channel0 selected.
 *            ADC_Channel_1 - ADC Channel1 selected.
 *            ADC_Channel_2 - ADC Channel2 selected.
 *            ADC_Channel_3 - ADC Channel3 selected.
 *            ADC_Channel_4 - ADC Channel4 selected.
 *            ADC_Channel_5 - ADC Channel5 selected.
 *            ADC_Channel_6 - ADC Channel6 selected.
 *            ADC_Channel_7 - ADC Channel7 selected.
 *            ADC_Channel_8 - ADC Channel8 selected.
 *            ADC_Channel_9 - ADC Channel9 selected.
 *            ADC_Channel_10 - ADC Channel10 selected.
 *            ADC_Channel_11 - ADC Channel11 selected.
 *            ADC_Channel_12 - ADC Channel12 selected.
 *            ADC_Channel_13 - ADC Channel13 selected.
 *            ADC_Channel_14 - ADC Channel14 selected.
 *            ADC_Channel_15 - ADC Channel15 selected.
 *            ADC_Channel_16 - ADC Channel16 selected.
 *            ADC_Channel_17 - ADC Channel17 selected.
 *
 * @return  val - The Data conversion value.
 */
u16 Get_ADC_Average(u8 ch,u8 times)
{
    u32 temp_val=0;
    u8 t;
    u16 val;

    for(t=0;t<times;t++)
    {
        temp_val+=Get_ADC_Val(ch);
        Delay_Ms(5);
    }

    val = temp_val/times;

    return val;
}

/*********************************************************************
 * @fn      Get_ConversionVal
 *
 * @brief   Get Conversion Value.
 *
 * @param   val - Sampling value
 *
 * @return  val+Calibrattion_Val - Conversion Value.
 */
u16 Get_ConversionVal(s16 val)
{
    if((val+Calibrattion_Val)<0) return 0;
    if((Calibrattion_Val+val)>4095) return 4095;
    return (val+Calibrattion_Val);
}

/*********************************************************************
 * @fn      main
 *
 * @brief   Main program.
 *
 * @return  none
 */
int main(void)
{
    u16 ADC_val,i;
    u16 DAC_OUT[6]={0,100,500,1000,2000,3000};
    SystemCoreClockUpdate();
    Delay_Init();
	USART_Printf_Init(115200);	
	printf("SystemClk:%d\r\n",SystemCoreClock);
	printf( "ChipID:%08x\r\n", DBGMCU_GetCHIPID() );
	printf("OPA Test\r\n");
	printf("CalibrattionValue:%d\n", Calibrattion_Val);
	Dac_Channel1_Init();
	OPA4_Init();
	ADC_Channel0_Init();

    while(1)
   {
        for(i=0;i<6;i++)
        {
            DAC_SetChannel1Data(DAC_Align_12b_R, DAC_OUT[i]);
            ADC_val = Get_ADC_Average( ADC_Channel_0, 10 );
            printf( "OPA_OUT:%04d\r\n", ADC_val);
            printf( "OPA_OUT:%04d\r\n", Get_ConversionVal(ADC_val+Calibrattion_Val));
            Delay_Ms(500);
        }
   }
}

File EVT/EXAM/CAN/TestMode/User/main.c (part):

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/*
 *@Note
 *CAN test mode, including silent mode, loopback mode and loopback silent mode:
 *CAN1-CAN_Tx(PB9),CAN_Rx(PB8)
 *CAN2-CAN_Tx(PB13),CAN_Rx(PB12)
 *Standard_Frame: includes a 32bit filter mask bit pattern.
 *
 */
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
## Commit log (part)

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2021-12-27 first release
    CH32V20x_30xDS0.PDF // CH32V307 DATASHEET
    CH32V307EVT.zip // CH32V307 SDK and HDK
    CH32V307EVT_structure.txt //Read me of CH32V307 SDK/HDK
2022-01-08 Structural optimization
2022-01-20 new application, add 8_uart_server demo
2022-01-20 add README.md
2022-01-20 1.updata EVT 2.add SCHPCB
2022-01-20 1.EVT updata add file 2.add SCHPCB
2022-01-21 update rtt demo
2022-01-24 add file SCH_PCB - CH32V307V-R0.pdf SCH_PCB - CH32V307V-R1.pdf
2022-01-24 update readme
    update readme
2022-01-26 fix the typo,update README.md
2022-01-27 updata 1.updata EVT
2022-01-28 updata User sheet
2022-04-13 Updata 1.EVT 2.Application->USB_CDC+HID 3.Datasheet->Change to UDR
2022-04-13 updata--
2022-04-13 updata
2022-04-27 WCH-ISP-Tool
    WCH ISP TOOL FOR ALL WCH MCUs
2022-06-08 updata EVT
2022-06-09 add WCH-Link
2022-06-09 updata list
2022-06-09 updata USB HID+CDC_Device
2022-06-09 delet
2022-06-10 updata-list EN
2022-09-04 Correcting type SysTic'K' -> SysTick
2022-11-06 EVT-V1.9
2023-01-04 add WCH-LinkUserManual-EN.PDF
2023-01-18 updata-EVT-V2.0
2023-01-31 Updata URL-DataSheet，SCHPCB，WCH-Link
2023-01-31 add QingKeV4_Processor_Manual.PDF
2023-05-26 updata-Link
2023-12-01 V2.3
2024-03-12 V2.4
2024-05-09 v2.5
2024-06-14 fix warnning -Wstrict-prototypes
2024-07-12 V2.6
2024-08-29 updata link picture
2024-11-21 V2.7
2025-04-25 V2.8
